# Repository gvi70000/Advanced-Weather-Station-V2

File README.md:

Advanced Weather Station V2
The Advanced Weather Station V2 is a high-precision environmental monitoring system designed for professional-grade reliability and scientific accuracy. Building upon the success of the first version, V2 introduces significant hardware optimizations and a more powerful processing architecture to deliver even better performance in the field.

Key Improvements in V2
Upgraded MCU: Now powered by the STM32G431, providing enhanced processing capabilities, better power efficiency, and advanced peripherals compared to the previous generation.

Streamlined Communication: All Programmable Gain Amplifiers (PGAs) are now consolidated on a single UART bus, simplifying the communication protocol and reducing cable complexity.

Enhanced PCB Design: A completely overhauled PCB layout featuring improved signal integrity, better thermal management, and a more compact, robust form factor for long-term outdoor deployment.

Overview
This weather station integrates a comprehensive suite of high-precision sensors to monitor atmospheric conditions, air quality, and spatial positioning. It leverages ultrasonic technology for maintenance-free wind measurement and GNSS RTK for centimetre-level location accuracy.

Features & Sensors
Ultrasonic Wind Measurement: Precise wind speed and direction without moving parts.

GNSS RTK: High-precision positioning for mobile or stationary research.

Environmental Suite:

UV & Ambient Light: UV radiation and light intensity monitoring.

Air Quality: ScioSense ENS160 for CO2 and VOC detection.

Lightning Detection: ScioSense AS3935 for storm activity tracking.

Pressure & Temp: Bosch BMP581 for barometric accuracy.

Humidity: Dual TI HDC3020 sensors for redundant climate analysis.

Rugged Construction: Optical sensors are protected by UV-transparent glass, and the ultrasonic assembly uses 304 stainless steel and ASA 3D-printed enclosures.

Workflow
Data Acquisition: Sensors collect raw environmental data, including wind vectors, gas concentrations, and radiation levels.

Processing: The STM32G431 aggregates the data, applies calibration constants, and handles temperature compensation in real-time.

Connectivity: Processed data is transmitted via an ESP32-PoE interface to Ethernet networks, enabling seamless integration with MQTT brokers or cloud-based dashboards.

Applications
Climate & Scientific Research: Accurate data collection for long-term studies.

Smart Agriculture: Optimize irrigation and crop protection based on hyper-local weather.

Renewable Energy: Ideal for solar tracking and wind farm site assessment.

Smart Cities: Real-time air quality and environmental safety monitoring.

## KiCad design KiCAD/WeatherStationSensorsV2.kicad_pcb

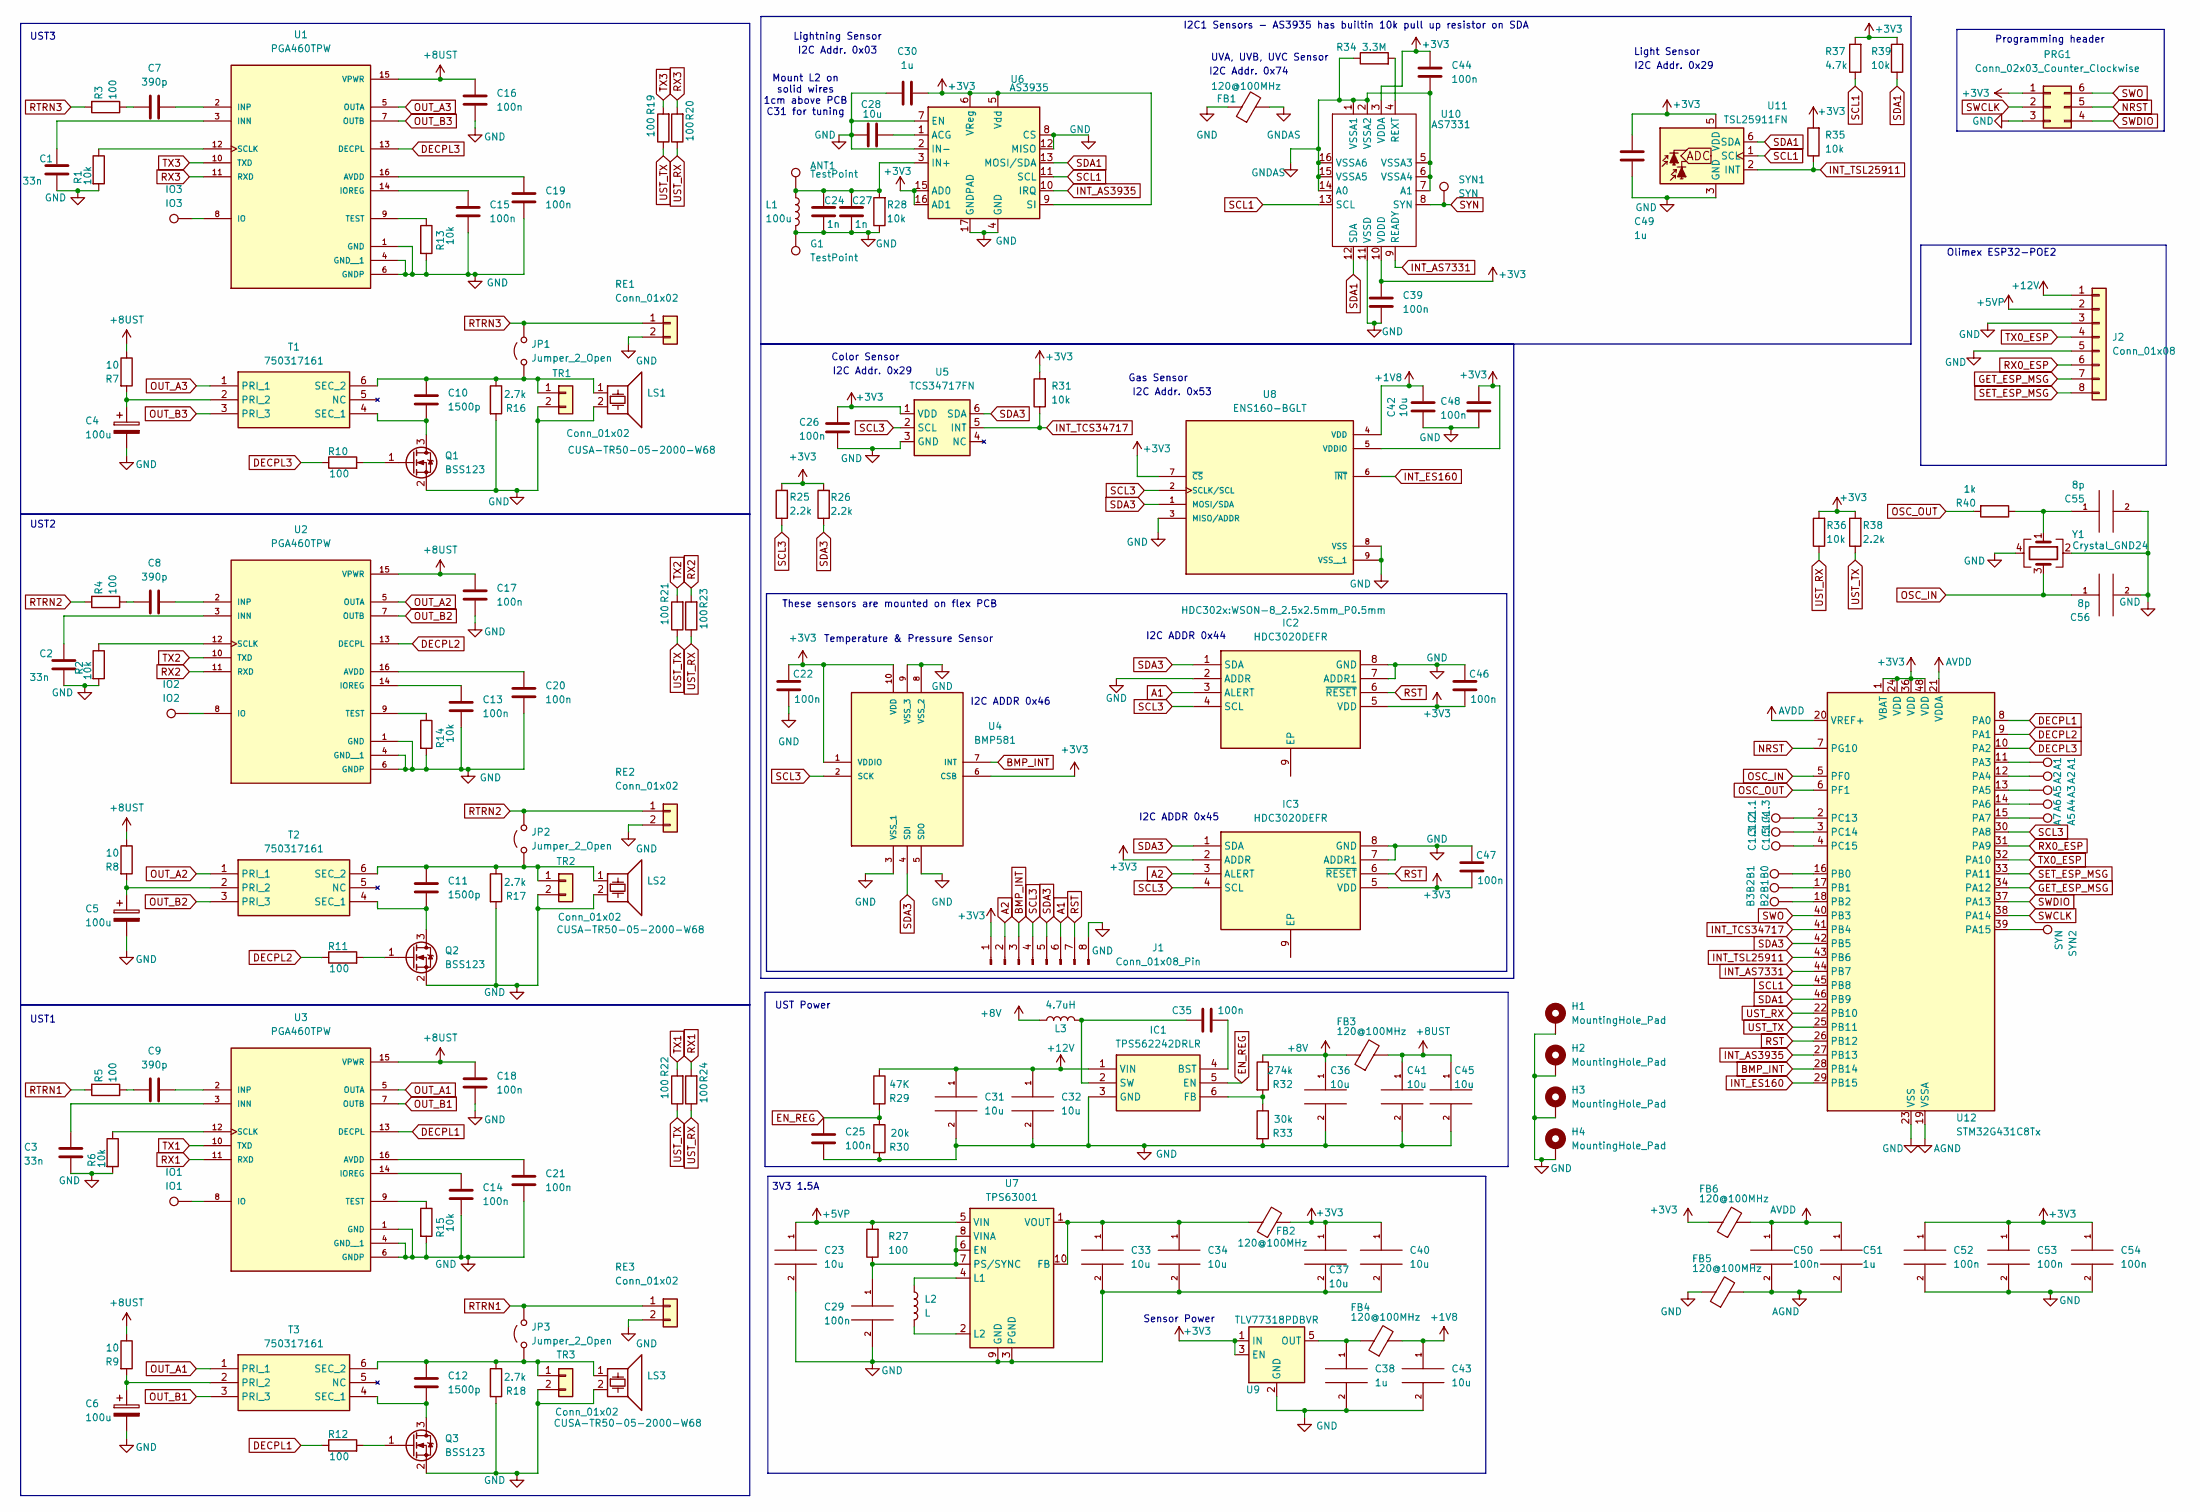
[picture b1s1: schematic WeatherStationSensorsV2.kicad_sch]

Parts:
A1: A1; TestPoint_Pad_D1.0mm
A2: A2; TestPoint_Pad_D1.0mm
A3: A5; TestPoint_Pad_D1.0mm
A4: A6; TestPoint_Pad_D1.0mm
A5: A7; TestPoint_Pad_D1.0mm
ANT1: TestPoint; TestPoint_THTPad_D1.5mm_Drill0.7mm
B1: B0; TestPoint_Pad_D1.0mm
B2: B1; TestPoint_Pad_D1.0mm
B3: B2; TestPoint_Pad_D1.0mm
C1, C2, C3: 33n; C_0805_2012Metric_Pad1.18x1.45mm_HandSolder
C1.1: C1.3; TestPoint_Pad_D1.0mm
C1.2: C1.4; TestPoint_Pad_D1.0mm
C1.3: C1.5; TestPoint_Pad_D1.0mm
C4, C5, C6: 100u; CP_Radial_D8.0mm_P3.50mm
C7, C8, C9: 390p; C_0805_2012Metric_Pad1.18x1.45mm_HandSolder
C10, C11, C12: 1500p; C_0805_2012Metric_Pad1.18x1.45mm_HandSolder
C13, C14, C15, C16, C17, C18, C19, C20, C21, C25, C26, C29, C35, C39, C44, C48, C50, C52, C53, C54: 100n; C_0805_2012Metric_Pad1.18x1.45mm_HandSolder
C22, C46, C47: 100n; C_0805_2012Metric
C23, C31, C32, C33, C34, C36, C37, C40, C41, C43, C45: 10u; C_1210_3225Metric_Pad1.33x2.70mm_HandSolder
C24, C27: 1n; C_0805_2012Metric_Pad1.18x1.45mm_HandSolder
C28, C42: 10u; C_0805_2012Metric_Pad1.18x1.45mm_HandSolder
C30, C38, C49, C51: 1u; C_0805_2012Metric_Pad1.18x1.45mm_HandSolder
C55, C56: 8p; C_0603_1608Metric_Pad1.08x0.95mm_HandSolder
FB1, FB2, FB3, FB4, FB5, FB6: 120@100MHz; R_0805_2012Metric_Pad1.20x1.40mm_HandSolder
G1: TestPoint; TestPoint_THTPad_D1.5mm_Drill0.7mm
H1, H2, H3, H4: MountingHole_Pad; MountingHole_3.2mm_M3_Pad_Via
IC1: TPS562242DRLR; SOTFL50P160X60-6N; Manufacturer_Part_Number TPS562242DRLR
IC2, IC3: HDC3020DEFR; WSON-8_2.5x2.5mm_P0.5mm; Mouser Part Number 595-HDC3020DEFR
IO1: IO1; TestPoint_Pad_D1.0mm
IO2: IO2; TestPoint_Pad_D1.0mm
IO3: IO3; TestPoint_Pad_D1.0mm
J1: Conn_01x08_Pin; Hirose_DF13-08P-1.25DSA_1x08_P1.25mm_Vertical
J2: Conn_01x08; PinHeader_1x08_P2.54mm_Vertical
JP1, JP2, JP3: Jumper_2_Open; SolderJumper-2_P1.3mm_Open_RoundedPad1.0x1.5mm
L1: 100u; Coilcraft_MA5532-AE_RFID
L2: L; CC453232A
L3: 4.7uH; L_Bourns_SDR0703-4R7KL
LS1, LS2, LS3: CUSA-TR50-05-2000-W68
PRG1: Conn_02x03_Counter_Clockwise; PinHeader_2x03_P2.54mm_Vertical
Q1, Q2, Q3: BSS123; SOT-23
R1, R2, R6, R13, R14, R15, R31, R35, R36, R39: 10k; R_0805_2012Metric_Pad1.20x1.40mm_HandSolder
R3, R4, R5, R10, R11, R12, R19, R20, R21, R22, R23, R24, R27: 100; R_0805_2012Metric_Pad1.20x1.40mm_HandSolder
R7, R8, R9: 10; R_0805_2012Metric_Pad1.20x1.40mm_HandSolder
R16, R17, R18: 2.7k; R_0805_2012Metric_Pad1.20x1.40mm_HandSolder
R25, R26, R38: 2.2k; R_0805_2012Metric_Pad1.20x1.40mm_HandSolder
R28: 10k; R_0603_1608Metric_Pad0.98x0.95mm_HandSolder
R29: 47K; R_0805_2012Metric_Pad1.20x1.40mm_HandSolder
R30: 20k; R_0805_2012Metric_Pad1.20x1.40mm_HandSolder
R32: 274k; R_0805_2012Metric_Pad1.20x1.40mm_HandSolder
R33: 30k; R_0805_2012Metric_Pad1.20x1.40mm_HandSolder
R34: 3.3M; R_0805_2012Metric_Pad1.20x1.40mm_HandSolder
R37: 4.7k; R_0805_2012Metric_Pad1.20x1.40mm_HandSolder
R40: 1k; R_0603_1608Metric_Pad0.98x0.95mm_HandSolder
RE1, RE2, RE3: Conn_01x02; PinHeader_1x02_P2.54mm_Vertical
SYN1, SYN2: SYN; TestPoint_Pad_D1.0mm
T1, T2, T3: 750317161; Mouser Part Number 710-750317161
TR1, TR2, TR3: Conn_01x02; PinHeader_1x02_P2.54mm_Vertical
U1, U2, U3: PGA460TPW; SOP65P640X120-16N; PARTREV B
U4: BMP581; Manufacturer_Part_Number BMP581
U5: TCS34717FN; FN6
U6: AS3935; MLPQ-16-1EP_4x4mm_P0.65mm_EP2.8x2.8mm
U7: TPS63001; Texas_DRC0010J_ThermalVias
U8: ENS160-BGLT; XDCR_ENS160-BGLT; PARTREV 1.3
U9: TLV77318PDBVR; SOT-23-5
U10: AS7331
U11: TSL25911FN; AMS_TSL25911FN
U12: STM32G431C8Tx; LQFP-48_7x7mm_P0.5mm
Y1: Crystal_GND24; Crystal_SMD_3225-4Pin_3.2x2.5mm_HandSoldering

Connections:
+1V8: C42.2, C43.1, FB4.2, U8.4 (VDD)
+3V3: C22.1, C26.1, C30.2, C37.1, C39.1, C40.1, C44.1, C46.2, C47.2, C48.1, C49.2, C52.1, C53.1, C54.1, FB2.2, FB6.1, IC2.5 (VDD), IC3.2 (ADDR), IC3.5 (VDD), J1.1, PRG1.1, R25.2, R26.2, R31.2, R35.2, R36.2, R37.2, R38.2, R39.2, U4.1 (VDDIO), U4.6 (CSB), U4.10 (VDD), U5.1 (VDD), U6.5 (Vdd), U6.6 (VReg), U6.9 (SI), U6.15 (AD0), U6.16 (AD1), U8.5 (VDDIO), U8.7 (~CS), U9.1 (IN), U9.3 (EN), U10.3 (VDDA), U10.10 (VDDD), U11.5 (VDD), U12.1 (VBAT), U12.24 (VDD), U12.36 (VDD), U12.48 (VDD)
+5VP: C23.1, J2.2, R27.2, U7.5 (VIN)
+8UST: C16.1, C17.1, C18.1, C41.1, C45.1, FB3.2, R7.1, R8.1, R9.1, U1.15 (VPWR), U2.15 (VPWR), U3.15 (VPWR)
+8V: C36.1, FB3.1, L3.1, R32.1
+12V: C31.1, C32.1, IC1.1 (VIN), J2.1, R29.1
A1: IC2.3 (ALERT), J1.6
A2: IC3.3 (ALERT), J1.2
AGND: C50.2, C51.2, FB5.2, U12.19 (VSSA)
AVDD: C50.1, C51.1, FB6.2, U12.20 (VREF+), U12.21 (VDDA)
BMP_INT: J1.3, U4.7 (INT), U12.28 (PB14)
DECPL1: R12.1, U3.13 (DECPL), U12.8 (PA0)
DECPL2: R11.1, U2.13 (DECPL), U12.9 (PA1)
DECPL3: R10.1, U1.13 (DECPL), U12.10 (PA2)
EN_REG: C25.1, IC1.5 (EN), R29.2, R30.1
GET_ESP_MSG: J2.7, U12.34 (PA12)
GND: C1.1, C2.1, C3.1, C4.2, C5.2, C6.2, C13.2, C14.2, C15.2, C16.2, C17.2, C18.2, C19.2, C20.2, C21.2, C22.2, C23.2, C24.2, C25.2, C26.2, C27.2, C28.2, C29.2, C30.1, C31.2, C32.2, C33.2, C34.2, C36.2, C37.2, C38.2, C39.2, C40.2, C41.2, C42.1, C43.2, C45.2, C46.1, C47.1, C48.2, C49.1, C52.2, C53.2, C54.2, C55.2, C56.2, FB1.1, FB5.1, G1.1, H1.1, H2.1, H3.1, H4.1, IC1.3 (GND), IC2.2 (ADDR), IC2.7 (ADDR1), IC2.8 (GND), IC3.7 (ADDR1), IC3.8 (GND), J1.8, J2.3, J2.5, L1.2, LS1.2, LS2.2, LS3.2, PRG1.3, Q1.2 (S), Q2.2 (S), Q3.2 (S), R1.2, R2.2, R6.2, R13.2, R14.2, R15.2, R16.2, R17.2, R18.2, R28.1, R30.2, R33.2, RE1.2, RE2.2, RE3.2, TR1.2, TR2.2, TR3.2, U1.1 (GND), U1.4 (GND__1), U1.6 (GNDP), U2.1 (GND), U2.4 (GND__1), U2.6 (GNDP), U3.1 (GND), U3.4 (GND__1), U3.6 (GNDP), U4.3 (VSS_1), U4.5 (SDO), U4.8 (VSS_2), U4.9 (VSS_3), U5.3 (GND), U6.2 (IN-), U6.4 (GND), U6.7 (EN), U6.8 (CS), U6.12 (MISO), U6.17 (GNDPAD), U7.3 (PGND), U7.9 (GND), U7.11 (PGND), U8.3 (MISO/ADDR), U8.8 (VSS), U8.9 (VSS__1), U9.2 (GND), U10.11 (VSSD), U11.3 (GND), U12.23 (VSS), U12.35 (VSS), U12.47 (VSS), Y1.2, Y1.4
GNDAS: C44.2, FB1.2, R34.1, U10.1 (VSSA1), U10.2 (VSSA2), U10.5 (VSSA3), U10.6 (VSSA4), U10.7 (A1), U10.14 (A0), U10.15 (VSSA5), U10.16 (VSSA6)
INT_AS3935: U6.10 (IRQ), U12.27 (PB13)
INT_AS7331: U10.9 (READY), U12.44 (PB7)
INT_ES160: U8.6 (~INT), U12.29 (PB15)
INT_TCS34717: R31.1, U5.5 (INT), U12.41 (PB4)
INT_TSL25911: R35.1, U11.2 (INT), U12.43 (PB6)
NRST: PRG1.5, U12.7 (PG10)
unnamed: C7.2, R3.1
unnamed: C8.2, R4.1
unnamed: C9.2, R5.1
unnamed: C55.1, R40.1, Y1.1
unnamed: C35.2, IC1.4 (BST)
unnamed: IC1.6 (FB), R32.2, R33.1
unnamed: C35.1, IC1.2 (SW), L3.2
unnamed: C10.1, JP1.1 (A), LS1.1, R16.1, T1.6 (SEC_2), TR1.1
unnamed: C11.1, JP2.1 (A), LS2.1, R17.1, T2.6 (SEC_2), TR2.1
unnamed: C12.1, JP3.1 (A), LS3.1, R18.1, T3.6 (SEC_2), TR3.1
unnamed: C10.2, Q1.3 (D), T1.4 (SEC_1)
unnamed: Q1.1 (G), R10.2
unnamed: C11.2, Q2.3 (D), T2.4 (SEC_1)
unnamed: Q2.1 (G), R11.2
unnamed: C12.2, Q3.3 (D), T3.4 (SEC_1)
unnamed: Q3.1 (G), R12.2
unnamed: C4.1, R7.2, T1.2 (PRI_2)
unnamed: C5.1, R8.2, T2.2 (PRI_2)
unnamed: C6.1, R9.2, T3.2 (PRI_2)
unnamed: C19.1, U1.16 (AVDD)
unnamed: C1.2, U1.3 (INN)
unnamed: C7.1, U1.2 (INP)
unnamed: IO3.1, U1.8 (IO)
unnamed: C15.1, U1.14 (IOREG)
unnamed: R1.1, U1.12 (SCLK)
unnamed: R13.1, U1.9 (TEST)
unnamed: C20.1, U2.16 (AVDD)
unnamed: C2.2, U2.3 (INN)
unnamed: C8.1, U2.2 (INP)
unnamed: IO2.1, U2.8 (IO)
unnamed: C13.1, U2.14 (IOREG)
unnamed: R2.1, U2.12 (SCLK)
unnamed: R14.1, U2.9 (TEST)
unnamed: C21.1, U3.16 (AVDD)
unnamed: C3.2, U3.3 (INN)
unnamed: C9.1, U3.2 (INP)
unnamed: IO1.1, U3.8 (IO)
unnamed: C14.1, U3.14 (IOREG)
unnamed: R6.1, U3.12 (SCLK)
unnamed: R15.1, U3.9 (TEST)
unnamed: C28.1, U6.1 (ACG)
unnamed: ANT1.1, C24.1, C27.1, L1.1, R28.2, U6.3 (IN+)
unnamed: C29.1, R27.1, U7.6 (EN), U7.7 (PS/SYNC), U7.8 (VINA)
unnamed: C33.1, C34.1, FB2.1, U7.1 (VOUT), U7.10 (FB)
unnamed: L2.1, U7.4 (L1)
unnamed: L2.2, U7.2 (L2)
unnamed: C38.1, FB4.1, U9.5 (OUT)
unnamed: R34.2, U10.4 (REXT)
unnamed: A1.1, U12.11 (PA3)
unnamed: A2.1, U12.12 (PA4)
unnamed: A3.1, U12.13 (PA5)
unnamed: A4.1, U12.14 (PA6)
unnamed: A5.1, U12.15 (PA7)
unnamed: SYN2.1, U12.39 (PA15)
unnamed: B1.1, U12.16 (PB0)
unnamed: B2.1, U12.17 (PB1)
unnamed: B3.1, U12.18 (PB2)
unnamed: C1.1.1, U12.2 (PC13)
unnamed: C1.2.1, U12.3 (PC14)
unnamed: C1.3.1, U12.4 (PC15)
OSC_IN: C56.1, U12.5 (PF0), Y1.3
OSC_OUT: R40.2, U12.6 (PF1)
OUT_A1: T3.1 (PRI_1), U3.5 (OUTA)
OUT_A2: T2.1 (PRI_1), U2.5 (OUTA)
OUT_A3: T1.1 (PRI_1), U1.5 (OUTA)
OUT_B1: T3.3 (PRI_3), U3.7 (OUTB)
OUT_B2: T2.3 (PRI_3), U2.7 (OUTB)
OUT_B3: T1.3 (PRI_3), U1.7 (OUTB)
RST: IC2.6 (~RESET), IC3.6 (~RESET), J1.7, U12.26 (PB12)
RTRN1: JP3.2 (B), R5.2, RE3.1
RTRN2: JP2.2 (B), R4.2, RE2.1
RTRN3: JP1.2 (B), R3.2, RE1.1
RX0_ESP: J2.6, U12.31 (PA9)
RX1: R24.2, U3.11 (RXD)
RX2: R23.2, U2.11 (RXD)
RX3: R20.2, U1.11 (RXD)
SCL1: R37.1, U6.11 (SCL), U10.13 (SCL), U11.1 (SCL), U12.45 (PB8)
SCL3: IC2.4 (SCL), IC3.4 (SCL), J1.4, R25.1, U4.2 (SCK), U5.2 (SCL), U8.2 (SCLK/SCL), U12.30 (PA8)
SDA1: R39.1, U6.13 (MOSI/SDA), U10.12 (SDA), U11.6 (SDA), U12.46 (PB9)
SDA3: IC2.1 (SDA), IC3.1 (SDA), J1.5, R26.1, U4.4 (SDI), U5.6 (SDA), U8.1 (MOSI/SDA), U12.42 (PB5)
SET_ESP_MSG: J2.8, U12.33 (PA11)
SWCLK: PRG1.2, U12.38 (PA14)
SWDIO: PRG1.4, U12.37 (PA13)
SWO: PRG1.6, U12.40 (PB3)
SYN: SYN1.1, U10.8 (SYN)
TX0_ESP: J2.4, U12.32 (PA10)
TX1: R22.2, U3.10 (TXD)
TX2: R21.2, U2.10 (TXD)
TX3: R19.2, U1.10 (TXD)
UST_RX: R20.1, R23.1, R24.1, R36.1, U12.22 (PB10)
UST_TX: R19.1, R21.1, R22.1, R38.1, U12.25 (PB11)

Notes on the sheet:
3V3 1.5A
These sensors are mounted on flex PCB
UST1
I2C Addr. 0x74
UST2
Gas Sensor
I2C Addr. 0x53
Mount L2 on solid wires 1cm above PCB C31 for tuning
Lightning Sensor
I2C ADDR 0x45
Sensor Power
Temperature & Pressure Sensor
I2C ADDR 0x44
Programming header
I2C Addr. 0x03
UST3
Light Sensor
UVA, UVB, UVC Sensor
I2C1 Sensors - AS3935 has builtin 10k pull up resistor on SDA
I2C Addr. 0x29
Olimex ESP32-POE2
UST Power
I2C ADDR 0x46
Color Sensor

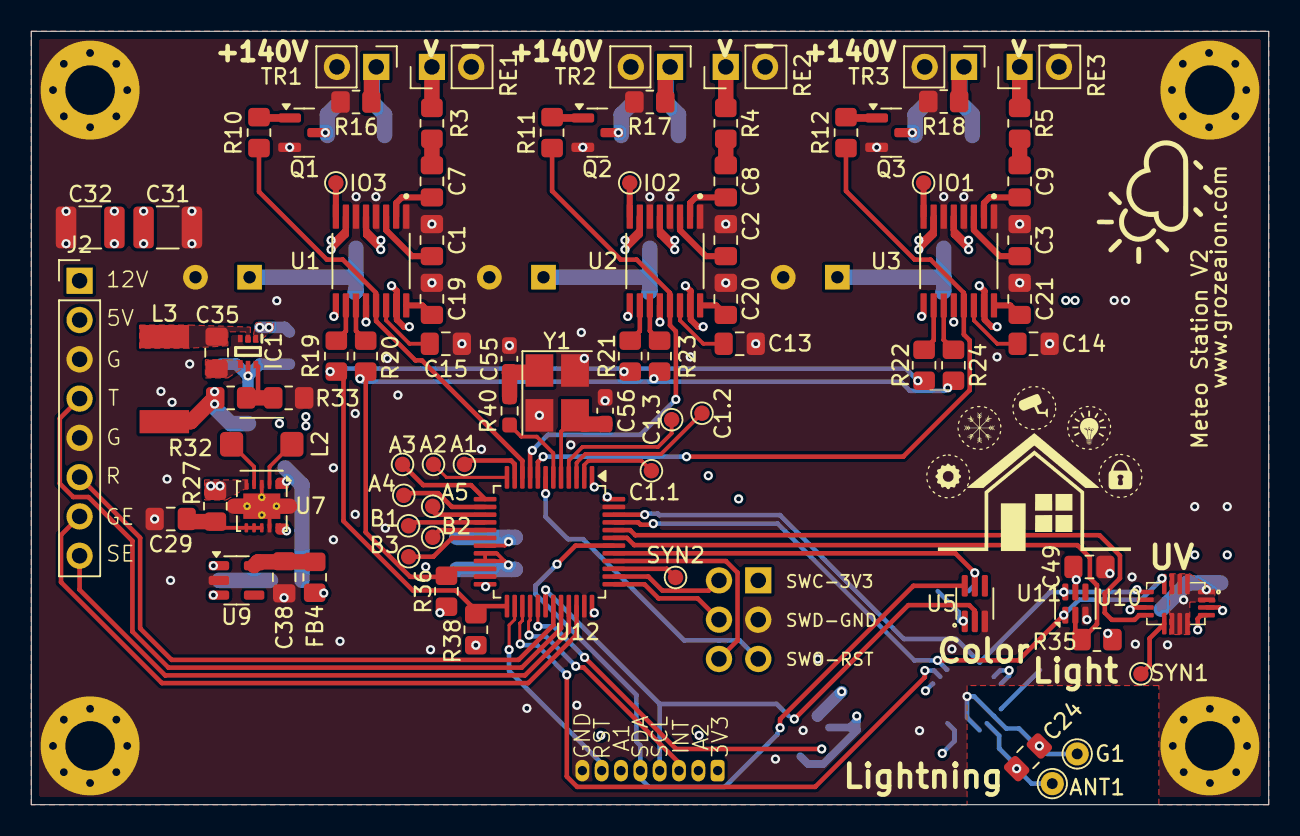
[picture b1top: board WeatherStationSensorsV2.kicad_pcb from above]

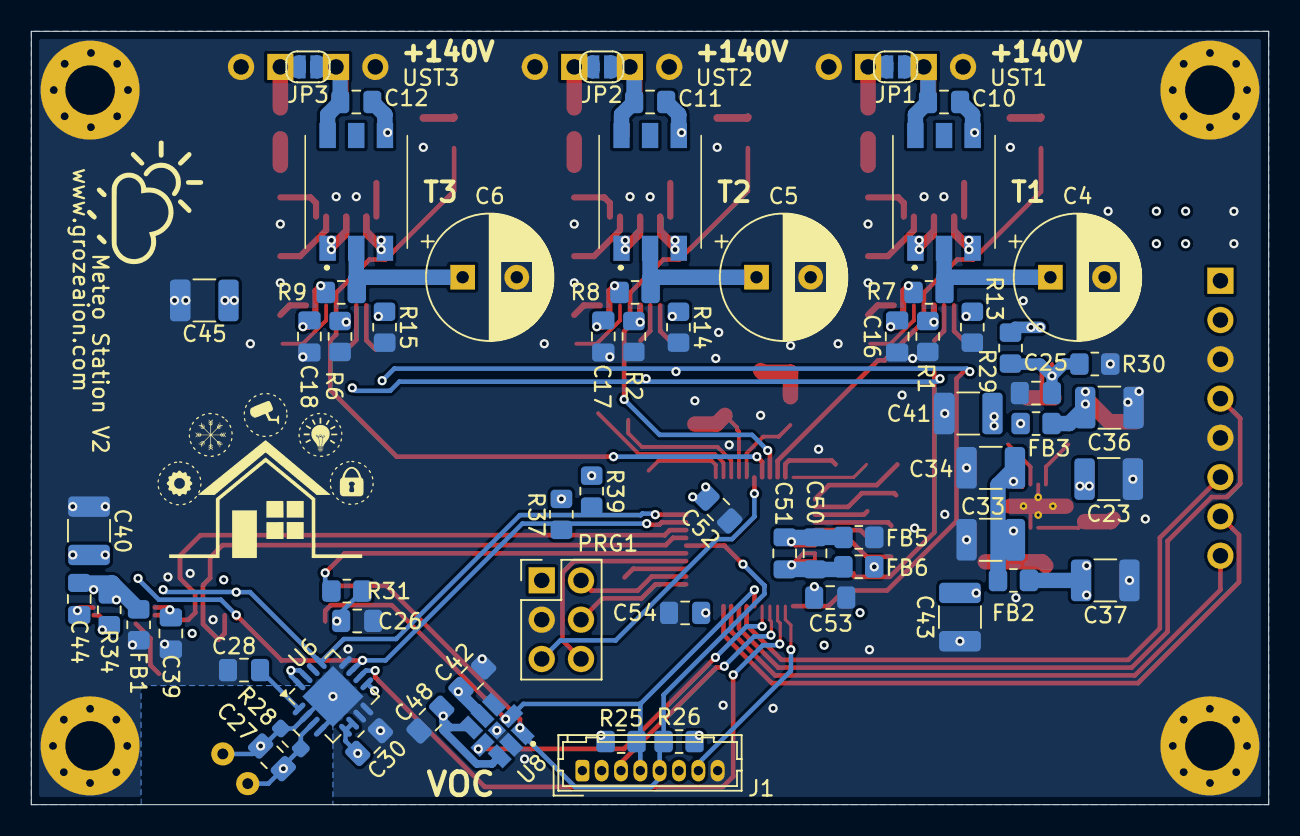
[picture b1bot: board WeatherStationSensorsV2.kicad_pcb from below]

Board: 4 copper layers, 80.0 x 50.0 mm, 154 parts (65 on the bottom side), 113 nets.

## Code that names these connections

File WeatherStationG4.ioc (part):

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Mcu.Name=STM32G431C(6-8-B)Tx
Mcu.Package=LQFP48
Mcu.UserName=STM32G431CBTx
PA0.GPIOParameters=GPIO_Label
PA0.GPIO_Label=DECPL0
PA0.Signal=S_TIM2_CH1
PA1.GPIOParameters=GPIO_Label
PA1.GPIO_Label=DECPL1
PA1.Signal=S_TIM2_CH2
PA10.GPIOParameters=GPIO_Label
PA10.GPIO_Label=ESP_TX
PA10.Mode=Asynchronous
PA10.Signal=USART1_RX
PA11.GPIOParameters=GPIO_Label
PA11.GPIO_Label=SET_ESP_MSG
PA11.Signal=GPIO_Output
PA13.Mode=Trace_Asynchronous_SW
PA13.Signal=SYS_JTMS-SWDIO
PA14.Mode=Trace_Asynchronous_SW
PA14.Signal=SYS_JTCK-SWCLK
PA2.GPIOParameters=GPIO_Label
PA2.GPIO_Label=DECPL2
PA2.Signal=S_TIM2_CH3
PA3.GPIOParameters=GPIO_Label
PA3.GPIO_Label=INT_AS3935
PA3.Signal=GPXTI3
PA5.GPIOParameters=GPIO_Speed,GPIO_Label
PA5.GPIO_Label=SGN
PA5.GPIO_Speed=GPIO_SPEED_FREQ_VERY_HIGH
PA5.Signal=GPIO_Output
PA8.Mode=I2C
PA8.Signal=I2C3_SCL
PA9.GPIOParameters=GPIO_Label
PA9.GPIO_Label=ESP_RX
PA9.Mode=Asynchronous
PA9.Signal=USART1_TX
PB10.GPIOParameters=GPIO_Label
PB10.GPIO_Label=UST_RX
PB10.Mode=Asynchronous
PB10.Signal=USART3_TX
PB11.GPIOParameters=GPIO_PuPd,GPIO_Label
PB11.GPIO_Label=UST_TX
PB11.GPIO_PuPd=GPIO_PULLUP
PB11.Mode=Asynchronous
PB11.Signal=USART3_RX
PB12.GPIOParameters=PinState,GPIO_Label
PB12.GPIO_Label=RST_HDC
PB12.PinState=GPIO_PIN_SET
PB12.Signal=GPIO_Output
PB14.GPIOParameters=GPIO_Label
PB14.GPIO_Label=BMP_INT
PB14.Signal=GPXTI14
PB15.GPIOParameters=GPIO_Label,GPIO_ModeDefaultEXTI
PB15.GPIO_Label=INT_ES160
PB15.GPIO_ModeDefaultEXTI=GPIO_MODE_IT_FALLING
PB15.Signal=GPXTI15
PB3.Mode=Trace_Asynchronous_SW
PB3.Signal=SYS_JTDO-SWO
PB4.GPIOParameters=GPIO_Label,GPIO_ModeDefaultEXTI
PB4.GPIO_Label=INT_TCS34003
PB4.GPIO_ModeDefaultEXTI=GPIO_MODE_IT_FALLING
PB4.Signal=GPXTI4
PB5.Mode=I2C
PB5.Signal=I2C3_SDA
PB6.GPIOParameters=GPIO_Label,GPIO_ModeDefaultEXTI
PB6.GPIO_Label=INT_TSL25911
PB6.GPIO_ModeDefaultEXTI=GPIO_MODE_IT_FALLING
PB6.Signal=GPXTI6
PB7.GPIOParameters=GPIO_Label
PB7.GPIO_Label=INT_AS7331
PB7.Signal=GPXTI7
PB8-BOOT0.Mode=I2C
PB8-BOOT0.Signal=I2C1_SCL
PB9.Mode=I2C
PB9.Signal=I2C1_SDA
PF0-OSC_IN.Mode=HSE-External-Oscillator
PF0-OSC_IN.Signal=RCC_OSC_IN
PF1-OSC_OUT.Mode=HSE-External-Oscillator
PF1-OSC_OUT.Signal=RCC_OSC_OUT
RCC.HSE_VALUE=16000000
RCC.SYSCLKFreq_VALUE=170000000
RCC.SYSCLKSource=RCC_SYSCLKSOURCE_PLLCLK
board=custom

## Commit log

2026-02-01 Enhance README with details on Advanced Weather Station V2
    Expanded the README to include detailed information about the Advanced Weather Station V2, including key improvements, features, workflow, and applications.
